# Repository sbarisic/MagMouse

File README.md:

# MagMouse

An open-source wired mouse exploring contactless Hall-sensed buttons with plastic
click mechanisms, and a motorized haptic scroll wheel.

**Active development: [four two-layer boards](hardware/two-layer/sandwich/README.md),
with two 70 Ã— 100 mm stacked Main boards and passive plastic button clicks.**
All four boards are routed, with independent schematics and clean native
ERC, DRC, connectivity and schematic-parity checks under the saved rules.
The [quote package](hardware/two-layer/sandwich/quote-package/README.md) contains
Gerbers, drills, BOMs and placement files; supplier and physical acceptance remain open.
The Main stack and Wheel harness each use 19 wires with three shared grounds.

Superseded boards, bench fixtures and quote packages are available in
[Git history](docs/history/README.md). The current checkout contains the active
designs, shared libraries, current manufacturing exports and retained evidence.

## V1 concept

- ESP32-S3 with native USB Full-Speed HID; target report interval: 1 ms.
- PMW3360DM-T2QU + LM19-LSI optical sensor for cursor movement; ICM-42688-P for supplementary motion.
- Three plastic click mechanisms provide tactile feedback and passive return.
  Each uses a TMAG5253 Hall sensor and a sensing magnet, read through ADS7038.
  Buttons have no coils or powered force feedback.
- MA735 angle sensing and a GB1806 motor driven by DRV8316R for scroll haptics.
- One USB-C cable for data and 5 V power, with force limits based on detected
  source capability. A powered Type-C hub/adapter is the intended full-power source.

## Repository map

| Directory | Contents |
| --- | --- |
| [hardware](hardware/README.md) | Electronics, preliminary BOM, schematic and PCB work |
| [mechanical](mechanical/README.md) | Housing, button mechanisms, scroll assembly |
| [firmware](firmware/README.md) | Embedded architecture and bring-up plan |
| [software](software/README.md) | Future PC configuration application |
| [docs](docs/README.md) | Requirements, interfaces, power and roadmap |

Start with the [architecture](docs/architecture.md), [interface plan](docs/interfaces.md),
and [button prototype plan](mechanical/button-mechanisms/README.md), then the
[roadmap](docs/roadmap.md). [ideas.md](ideas.md) preserves the original
brainstorming notes; the organized documents distinguish selected directions from
open engineering questions.

## Contributing and licensing

See [CONTRIBUTING.md](CONTRIBUTING.md). The next milestone is mechanical-interface
CAD, resulting PCB adjustments and whole-board review before manufacturing closure.

Hardware/mechanical: **CERN-OHL-S-2.0**. Firmware, PC software and supporting code:
**GPL-3.0-or-later**. General documentation: **CC-BY-SA-4.0**.
See [LICENSE.md](LICENSE.md) for scope and full texts.

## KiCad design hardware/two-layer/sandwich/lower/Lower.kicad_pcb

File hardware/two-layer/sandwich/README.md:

# MagMouse stacked two-layer boards

All four boards are routed and have independent schematics. Native KiCad 10.0.6
checks report zero ERC findings, DRC findings, unconnected items and schematic
parity findings under the saved rules. The [quote package](quote-package/README.md)
contains the files for supplier pricing; physical and supplier acceptance remain open.

The active boards use 1206 packages for all 193 resistors and ceramic capacitors
that previously used 0603 or 0805. Values and pin/net assignments are unchanged.
[1206-PARTS.md](1206-PARTS.md) lists the replacement manufacturer part numbers,
ratings and sourcing status. [1206-review.json](1206-review.json) records the
earlier package migration; [assembly-spacing-review.json](assembly-spacing-review.json)
records the subsequent 2 mm component spacing and outline changes.

The standard-via revision uses 0.30 mm via drills and at least 0.45 mm copper
lands. All four boards are checked for via-hole/SMD-land overlaps. The derived
[238 × 114 mm panel](panel/Panel.kicad_pcb) combines one of each board using
2 mm routed gaps and 5 mm mouse-bite tabs. Source copper is copied exactly,
with isolated net names for each board; individual outlines remain unchanged.

| Board/project | Dimensions | Copper layers | Original circuit footprints | Added interface/mount footprints |
| --- | --- | ---: | ---: | ---: |
| [Lower](lower/Lower.kicad_pro) | 70 × 100 mm, tapered | 2 | 122 | 6 |
| [Upper](upper/Upper.kicad_pro) | 70 × 100 mm, tapered | 2 | 86 | 6 |
| [Wheel](wheel/Wheel.kicad_pro) | 70 × 67 mm, clipped Main profile | 2 | 87 | 0 |
| [Encoder](../encoder/Encoder.kicad_pro) | 14 × 18 mm, two 4 mm upper chamfers | 2 | 3 | 0 |

[All-board overview](all-boards.png). Component footprints, pads and drills are
full size. Both Main outlines retain the approved taper and 38.5 mm front edge.
Wheel follows the Main sidewalls between y = 26 and 93 mm. Its 4,448 mm² outline adds 1,148 mm² to the previous rectangle. Wheel coordinates plus (7.5, 29) mm align it with Main in plan view. Stack height and Wheel mounting need mechanical fit confirmation.

[Wheel power and ground review](routing-review/POWER-GROUND.md) covers trace necks, via barrels, GND pours and the reordered brake feedback resistors.

[3D exports](3d/README.md) include STEP, GLB and angled previews for each board
and the panel, plus bare substrate STEP files. The populated exports include
available library models; the coverage report identifies 14 missing component
bodies. These are PCB models, not a mechanically positioned mouse assembly.

## Circuit and schematic split

Lower contains the ESP32, USB connector and data/CC circuitry, 3.3 V regulator,
optical sensor and local supplies, IMU, RGB, encoder interface and Wheel signal
connector J8. Upper contains the eFuses, power monitoring, three Hall sensors,
ADC1, hardware interlock and Wheel power connector J10.

The independent [Lower schematic](lower/Lower.kicad_sch) and
[Upper schematic](upper/Upper.kicad_sch) each include `20_Stack_Harness` with the
actual signal/power arrays and mounting holes. PCB symbol paths match these
projects. The combined [Main circuit](main-circuit/Main.kicad_sch) is retained as
the migration reference; edit the independent projects for subsequent work.
Every retained component value and pin/net connection was compared with that
reference. USB data/CC and analog Hall/current-sense/ADC connections stay local
to their respective boards.

Buttons use passive plastic click mechanisms and one sensing magnet per Hall
sensor. The active design removes 38 button-only parts, including U4/U5/U6,
J2/J3/J4 and U17. ADC1 channels 3–5 are grounded spares; GPIO4–9 are unused.
U18 retains the shared HALL_EN gate. Wheel drive, interlock, ACT_5V protection
and shared storage remain. [passive-buttons.json](passive-buttons.json) records
the exact removed parts and pin changes. The older routed checkpoints retain
the superseded button-coil circuitry.

## Wiring

The Main stack has **19 wires with three shared grounds**:

| Interface | Signals/supplies | Grounds | Total |
| --- | ---: | ---: | ---: |
| J101 ↔ J102 | 13 signals | 1 | 14 |
| J103 ↔ J104 | 3 supply rails | 2 | 5 |

Connect equal pad numbers using [WIRE_MAP.md](WIRE_MAP.md). Signal arrays are
2 × 7 at 2.54 mm pitch: x = 6/8.54 mm, y = 42–57.24 mm, 1.8 mm lands and
0.8 mm drills. Five power pads use 5.08 mm pitch at x = 25–45.32 mm,
2.4 mm lands and 1.2 mm drills. Both power arrays moved together to y = 12.25 mm
to provide assembly space below USB. Raw VBUS goes up, PWR_5V returns to Lower and
+3V3 goes back up. ACT_5V stays on Upper and feeds Wheel.

The Wheel harness also has **19 wires with three shared grounds**. Lower J8
and Wheel J9 each use 17 pads in a 2 × 9 grid with one hole omitted; their copper
envelope is 22.12 × 4.34 mm. Upper J10 and Wheel J11 carry ACT_5V and the third
ground. See [WHEEL_WIRE_MAP.md](WHEEL_WIRE_MAP.md). Wire gauges, cut lengths and
stack height still depend on the mechanical assembly.

## Placement and routing

Separate front components have at least 2 mm between their body-and-solder-land
envelopes. This does not change the pitch of pins within an IC or wire array;
copper-only test access is excluded from the component spacing measurement.
The circled Upper passive group has at least 3 mm clearance to the board edge.
The layouts retain the USB, optical, Hall, antenna and mounting datums. The two
stack power arrays move together by 1.25 mm; their pitch and pin map are unchanged.
Other parts and colliding front test pads move as recorded in the spacing review.
Fitted electronic parts remain on the front; several diagnostic test pads are
on the back. Encoder retains its sensor and wire-array positions; its two
4 × 4 mm chamfers remove 16 mm², reducing outline area from 252 to 236 mm².

The long USB pair was placed before routing, around the right side of the
optical reserve, using the inherited 1.10 mm trunk width and 0.15 mm nominal
gap with narrow land escapes. The 1206 revision retains that corridor and adapts
the resistor-end escape. Freerouting 2.5.0 and local geometric routing helpers
rebuilt connections affected by the larger packages. KiCad then checked minimum
track/via sizes, filled and stitched ground copper,
removed unused fanout vias, and checked actual connectivity and clearances.
Power escapes were widened where geometry permits. The fabricator's stack and
physical USB, power, thermal and analog performance still need verification.

Aligned M2 mounting candidates remain at (18,6), (52,6), (7,76), (63,76) mm:
2.2 mm holes and 5 mm support envelopes. Lower now has a real 17.26 × 8.60 mm
optical opening on Edge.Cuts, following PixArt PMW3360 datasheet R1.50 Figure 3.
In board coordinates it spans x = 31.20–39.80 and y = 43.68–60.94 mm; U35's
optical center remains (35.5,52.5) mm. Internal corners use R1 mm for the panel's
nominal 2 mm router; this corner geometry requires lens-fit confirmation.
The lens faces downward through Lower,
so this does not add a duplicate opening to Upper. Lens retention and stack
height still need mechanical fit confirmation. U3 stays at (35,89.25) mm,
with its antenna approximately 0.43 mm from
the curved board edge at the corners. The requested 5 mm reserve is
x = 22.3–47.7, y = 94.5–104 mm on both boards, extending beyond the rear edge.
Upper retains substrate over that region; assembled radio performance is untested.

## Validation and quote files

[routing-review/summary.json](routing-review/summary.json) records current board
hashes, sizes, layer counts, ERC/DRC/parity results and fabrication dimensions.
The native reports, exported netlists, front/back copper SVGs and track-width
measurements are alongside it. Inherited ignored categories remain explicit in
the reports; no new DRC or ERC exclusions were added for routing.

[MagMouse-quote-package.zip](MagMouse-quote-package.zip) includes four separate
Gerber/drill ZIPs, per-board BOM/CPL CSVs, combined purchasing inventory, manual
items and via-in-pad intersection lists. Read its [quotation notes](quote-package/README.md)
for stack, assembly, stock, shipping/tax and mechanical assumptions. This is a
pricing package. The [first live quote](quotes/2026-11-04-jlcpcb/QUOTE.md) records
the superseded 0.20 mm, separate-board version. The [standard-via panel quote](quotes/2026-11-04-panel-standard-vias/QUOTE.md)
was EUR 42.83 for five complete sets, or USD 99.25 delivered by EuroPacket DDP
to Croatia (4 November 2026). That quote predates the 1206 migration and has not
been refreshed for these files. No fabrication order is placed.

`partition.json` preserves ownership and the checked 19-wire contract.
`placement-positions.json`, `spacing-review.json`, `spacing-baseline.json`,
`placement.svg/png` and `passive-validation.json` are historical pre-routing
evidence; their old board hashes and airwire counts are not current route results.

## Reproduction

Use KiCad 10 Python. Edit the independent KiCad projects for future circuit or
layout changes. The one-time split and obsolete placement generators are now
in [Git history](../../../docs/history/README.md). Shared libraries and helper
functions live in [hardware/common](../../common/README.md).

`route_main.py` exports/imports Specctra sessions, `route_usb.py` defines the
initial USB corridor, `finish_main.py` fills and stitches ground, and
`widen_power.py` widens power where clearance and keepouts allow. Freerouting
2.5.0 used neck retry at 150 µm with the optimizer disabled for Lower. Lower's
DSN clearance was increased to 165 µm to leave margin for native minimum-width
restoration; saved KiCad clearances remain unchanged. Temporary sessions, router
binaries and logs stay in ignored `build/sandwich/main-routing`.

`export_quote.py` rechecks all four boards before exporting the package and
compares Main pins against the retained migration reference. `overview.py`
renders placement views; add `--main-only --copper` for the routed Main image.
The netlist and schematic-parity checks cover the current Wheel harness.
The obsolete harness conversion script is retained in Git history.

`standard_vias.py` records the one-time drill migration and assists local via
relocation; `repair_wheel.py` and `continuous_routes.py` provide local path repairs.
`standard-via-review.json` is historical evidence for the pre-1206 revision. It records unchanged component placement and pad/net identity,
unchanged motor-phase/brake copper, and the final drill and via-in-pad counts. The finished
KiCad boards are the editable source. `panelize.py` derives and verifies the
combined manufacturing panel and exports its Gerbers/drills. Its verification
compares every source pad, track, via drill and filled-zone vertex after translation,
checks connected substrate and router access, and runs native panel DRC.

`large_passives.py` performs the guarded one-time 1206 migration and verifies it
against the saved pre-migration snapshots in ignored `build/sandwich/1206`.
`1206-migration.json` records the per-reference purchasing substitutions;
`1206-review.json` records the final checks and source hashes. Do not rerun
the migration on an already converted project. `region_routes.py` supports
local two-layer repairs; every saved result still requires native KiCad DRC.

The fabrication rules explicitly use JLCPCB's 0.075 mm via annular ring and
0.20 mm via-hole-to-copper clearance, replacing 0.125/0.25 mm in the earlier
revision. Via hole-to-hole clearance stays 0.25 mm, copper clearance stays
0.15 mm by net class (0.127 mm board minimum), and minimum track width stays
0.127 mm. No additional DRC categories are ignored. These limits are based on
[JLCPCB's published capabilities](https://jlcpcb.com/capabilities/pcb-capabilities/).

Hardware: CERN-OHL-S-2.0. Scripts: GPL-3.0-or-later. Documentation: CC-BY-SA-4.0.

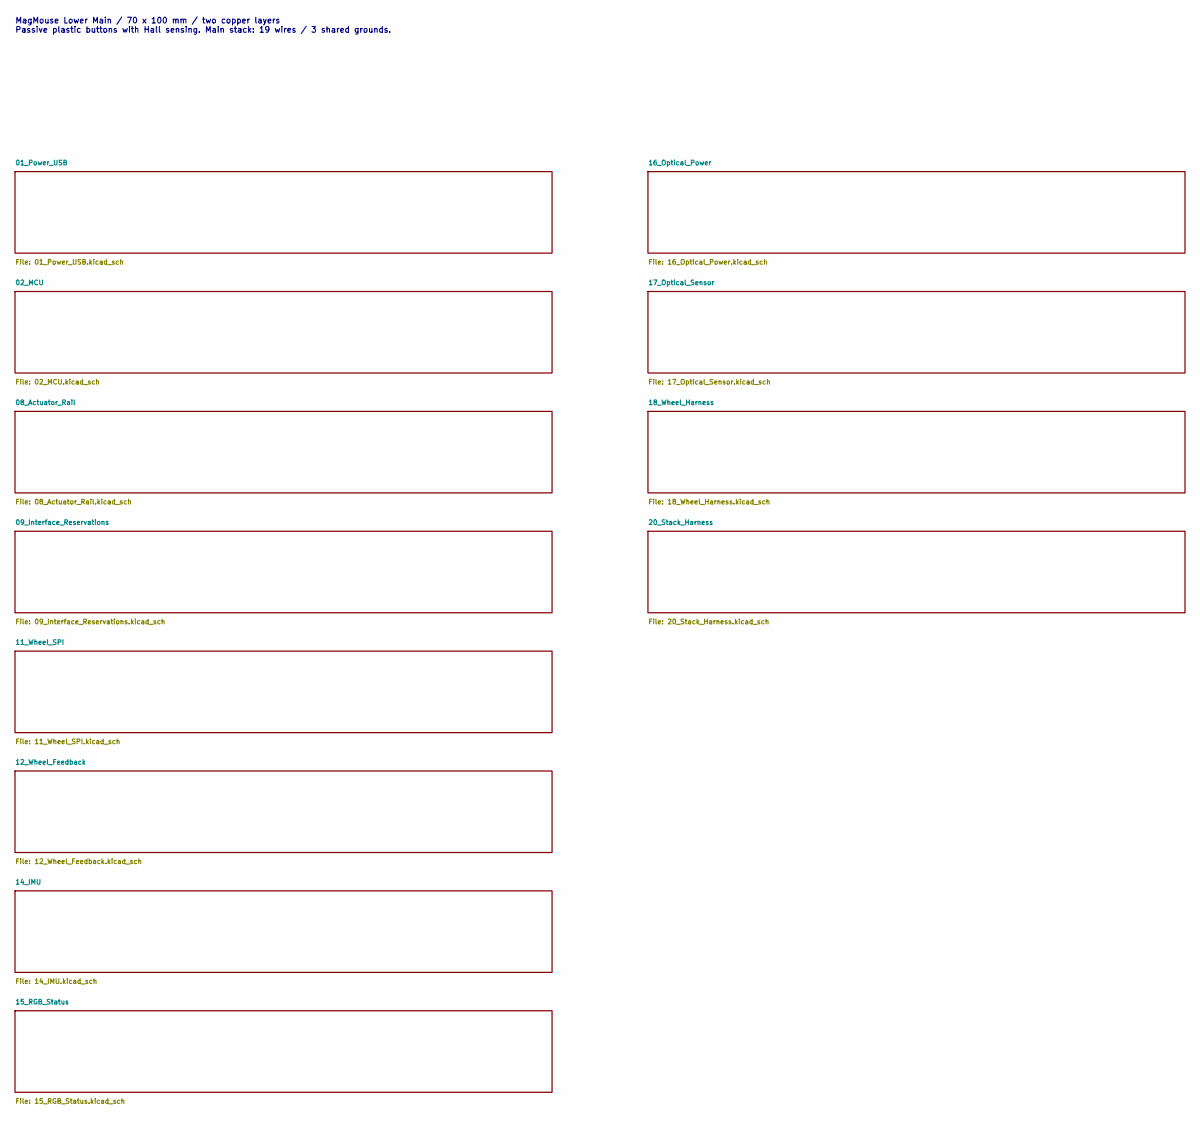
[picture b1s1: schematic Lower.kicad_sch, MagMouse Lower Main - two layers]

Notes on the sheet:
MagMouse Lower Main / 70 x 100 mm / two copper layers Passive plastic buttons with Hall sensing. Main stack: 19 wires / 3 shared grounds.

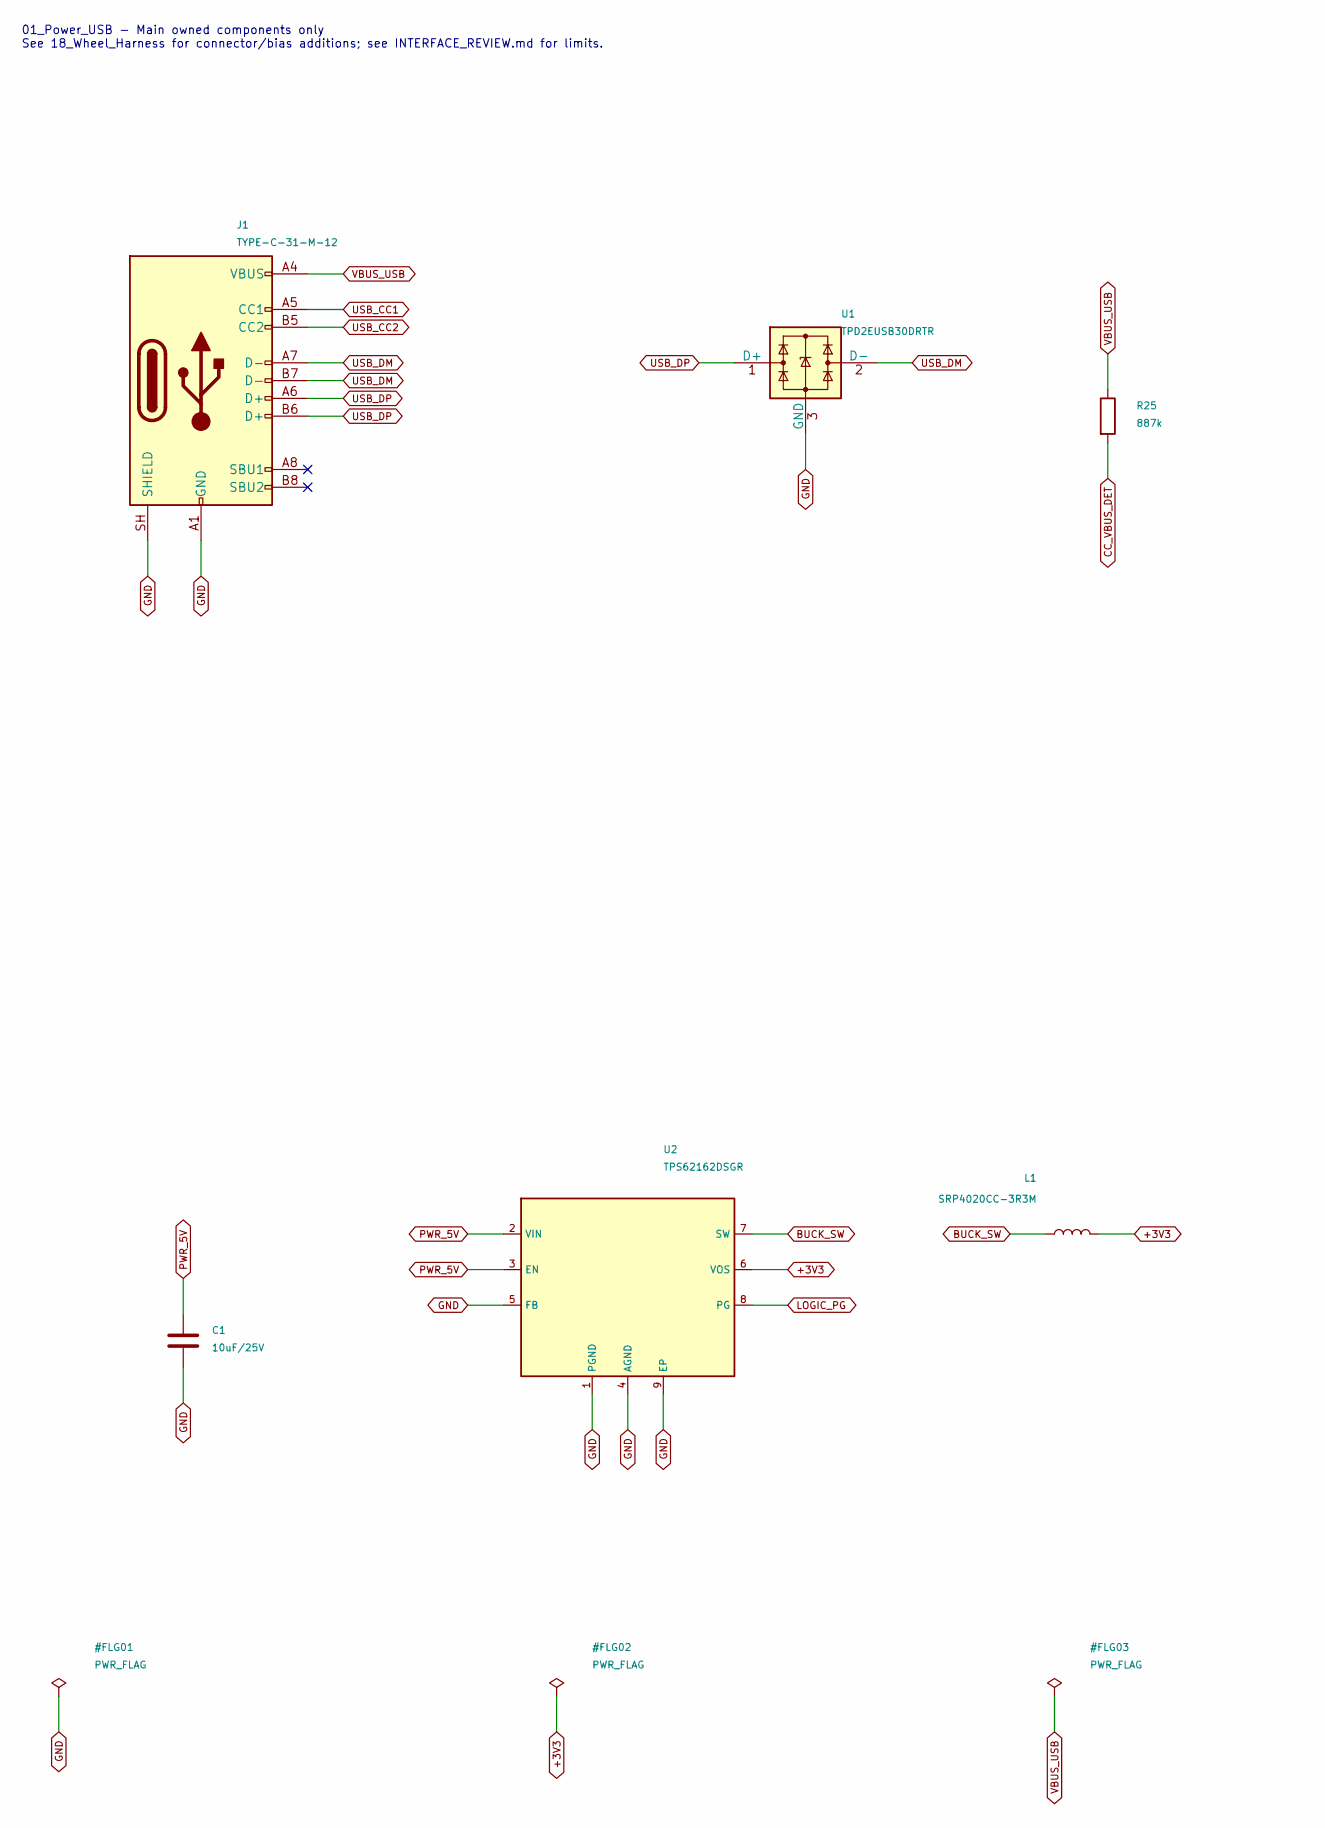
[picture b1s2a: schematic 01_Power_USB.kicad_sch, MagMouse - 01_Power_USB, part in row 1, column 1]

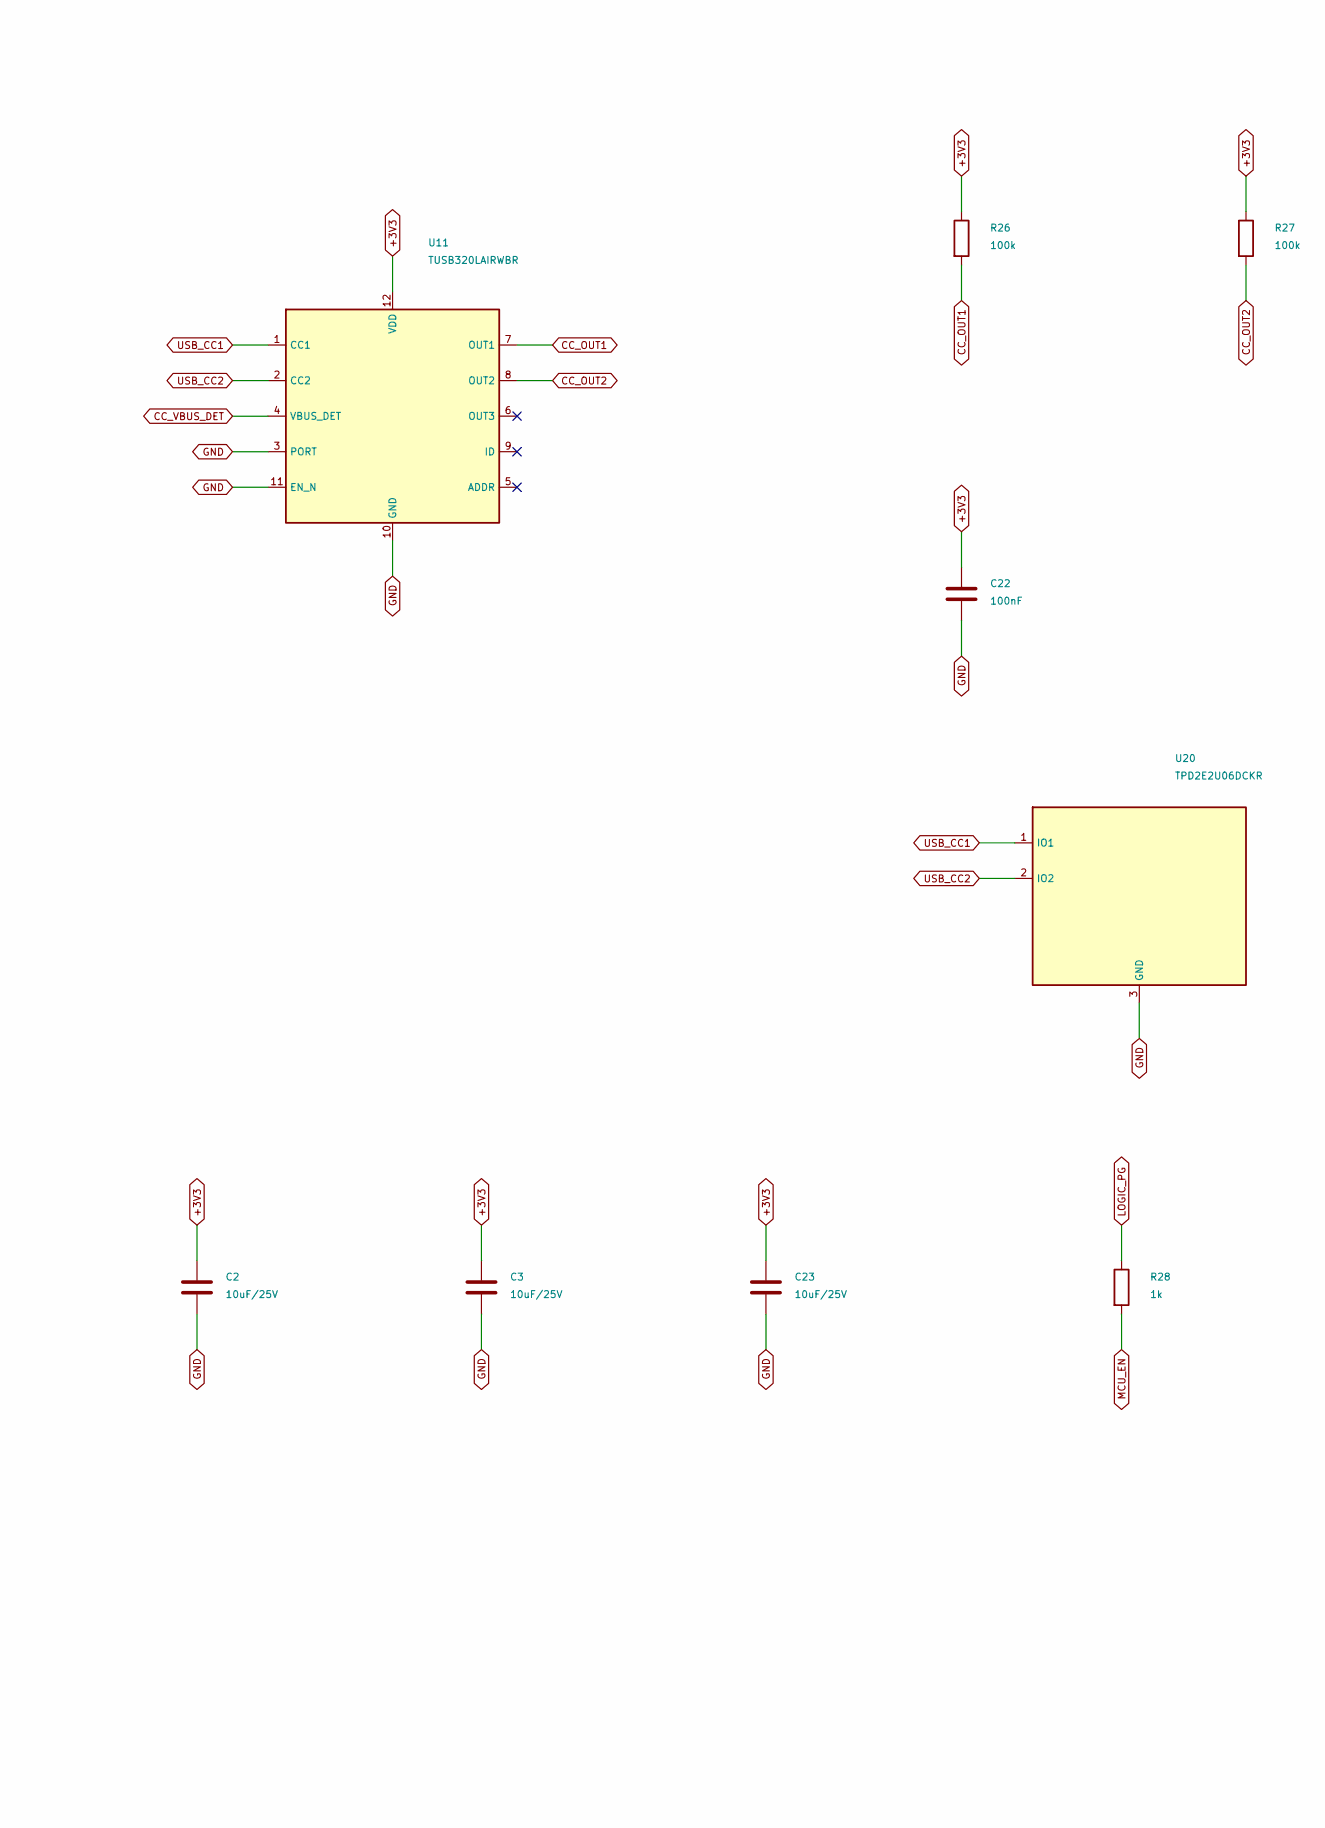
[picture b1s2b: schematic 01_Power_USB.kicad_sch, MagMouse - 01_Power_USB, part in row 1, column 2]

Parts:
C1, C2, C3, C23: 10uF/25V; C_1206_3216Metric; Rating 25 V, X5R, 10%; MPN CL31A106KAHNNNE
C22: 100nF; C_1206_3216Metric; Rating 50 V, X7R, 10%; MPN CC1206KRX7R9BB104
J1: TYPE-C-31-M-12; USB_C_Receptacle_HRO_TYPE-C-31-M-12; MPN TYPE-C-31-M-12; LCSC C165948
L1: SRP4020CC-3R3M; L_Bourns_SRP4020CC; MPN SRP4020CC-3R3M
R25: 887k; R_1206_3216Metric; Rating 0.25 W, 1%; MPN RC1206FR-07887KL
R26, R27: 100k; R_1206_3216Metric; Rating 0.25 W, 1%; MPN RC1206FR-07100KL
R28: 1k; R_1206_3216Metric; Rating 0.25 W, 1%; MPN RC1206FR-071KL
U1: TPD2EUSB30DRTR; Texas_DRT-3; MPN TPD2EUSB30DRTR; LCSC C97502
U2: TPS62162DSGR; Texas_DSG0008A_WSON-8-1EP_2x2mm_P0.5mm_EP0.9x1.6mm; MPN TPS62162DSGR; LCSC C40256
U11: TUSB320LAIRWBR; Texas_X2QFN-12_1.6x1.6mm_P0.4mm; MPN TUSB320LAIRWBR; LCSC C132554
U20: TPD2E2U06DCKR; SOT-323_SC-70; MPN TPD2E2U06DCKR; LCSC C1855726

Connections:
+3V3: C2.1, C3.1, C22.1, C23.1, L1.2, R26.1, R27.1, U2.6 (VOS), U11.12 (VDD); also elsewhere on the board
BUCK_SW: L1.1, U2.7 (SW)
CC_OUT1: R26.2, U11.7 (OUT1); also elsewhere on the board
CC_OUT2: R27.2, U11.8 (OUT2); also elsewhere on the board
CC_VBUS_DET: R25.2, U11.4 (VBUS_DET)
GND: C1.2, C2.2, C3.2, C22.2, C23.2, J1.A1 (GND), J1.A12 (GND), J1.B1 (GND), J1.B12 (GND), J1.SH (SHIELD), U1.3 (GND), U2.1 (PGND), U2.4 (AGND), U2.5 (FB), U2.9 (EP), U11.3 (PORT), U11.10 (GND), U11.11 (EN_N), U20.3 (GND); also elsewhere on the board
LOGIC_PG: R28.1, U2.8 (PG)
MCU_EN: R28.2; also elsewhere on the board
PWR_5V: C1.1, U2.2 (VIN), U2.3 (EN); also elsewhere on the board
USB_CC1: J1.A5 (CC1), U11.1 (CC1), U20.1 (IO1)
USB_CC2: J1.B5 (CC2), U11.2 (CC2), U20.2 (IO2)
USB_DM: J1.A7 (D-), J1.B7 (D-), U1.2 (D-); also elsewhere on the board
USB_DP: J1.A6 (D+), J1.B6 (D+), U1.1 (D+); also elsewhere on the board
VBUS_USB: J1.A4 (VBUS), J1.A9 (VBUS), J1.B4 (VBUS), J1.B9 (VBUS), R25.1; also elsewhere on the board

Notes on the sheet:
01_Power_USB - Main owned components only See 18_Wheel_Harness for connector/bias additions; see INTERFACE_REVIEW.md for limits.

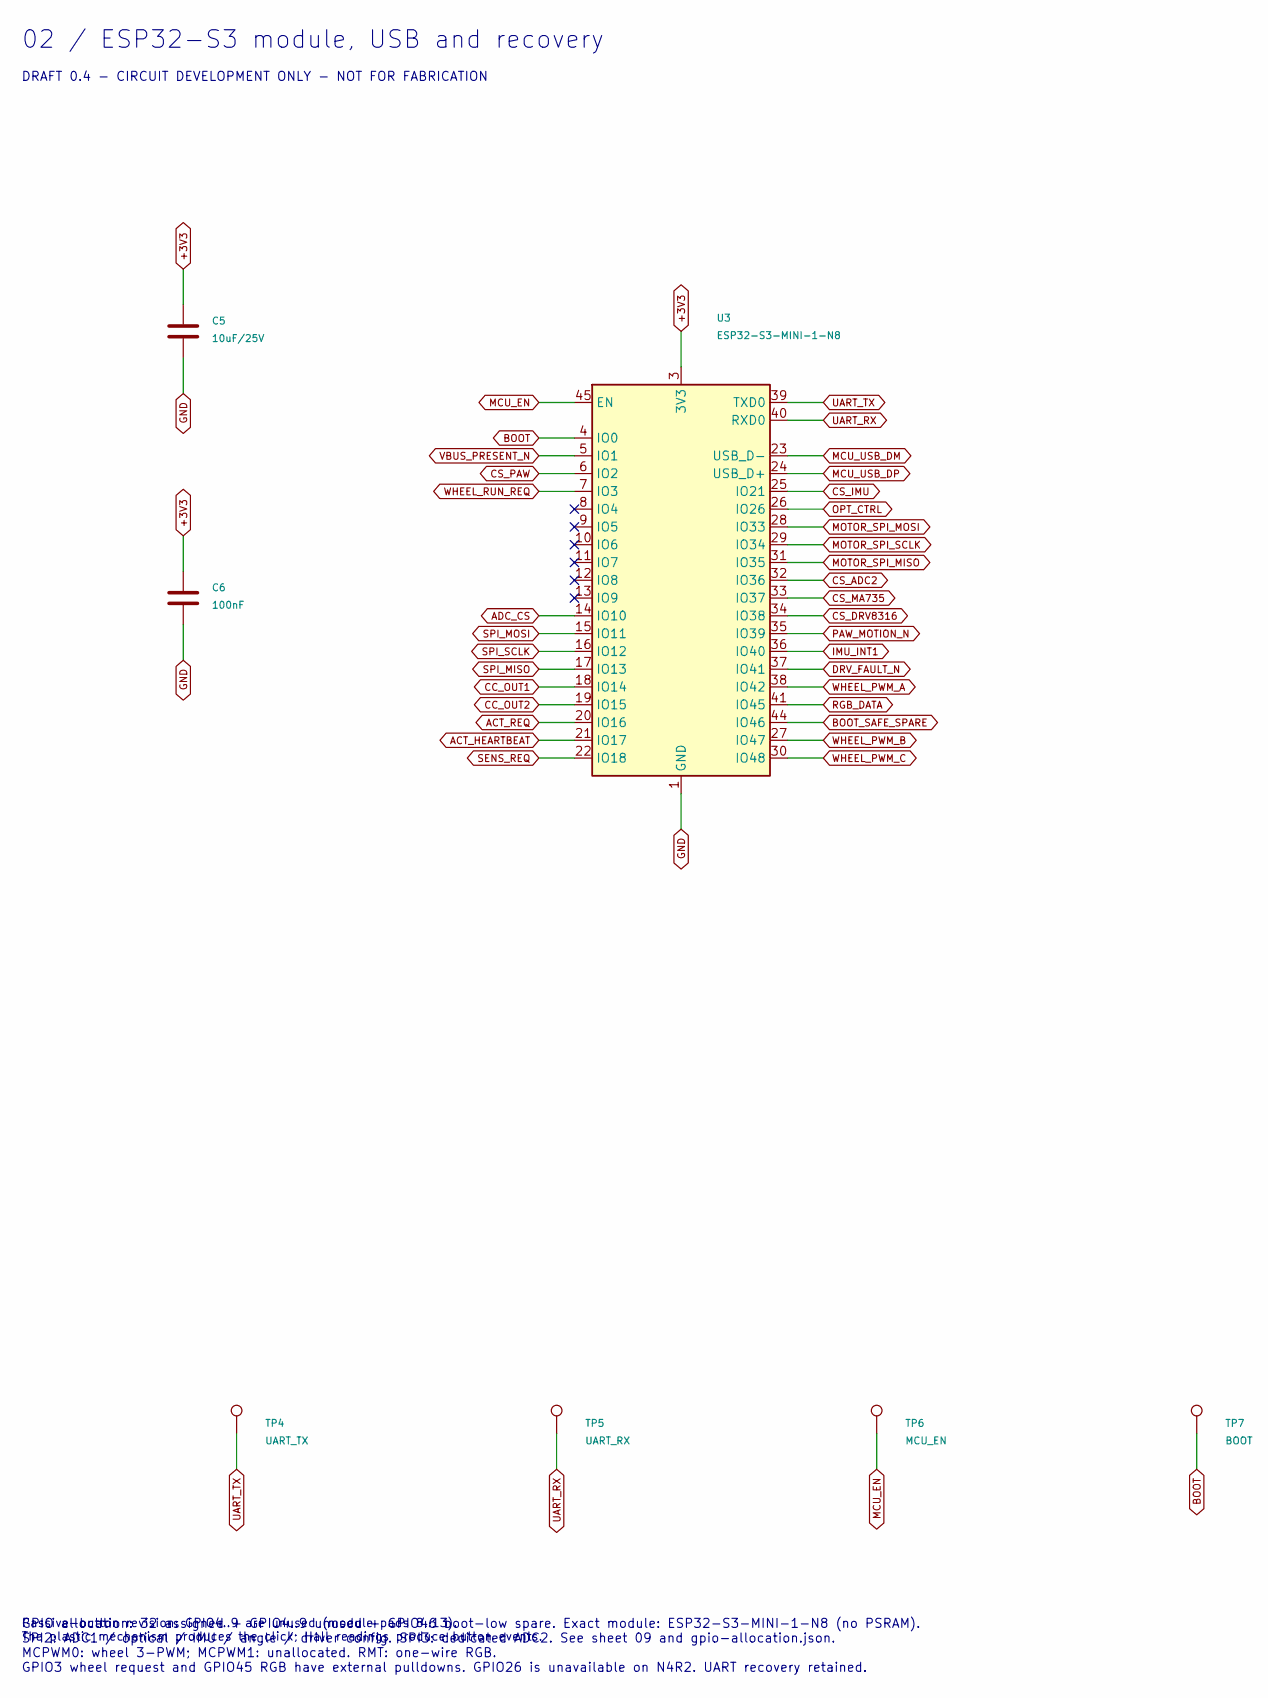
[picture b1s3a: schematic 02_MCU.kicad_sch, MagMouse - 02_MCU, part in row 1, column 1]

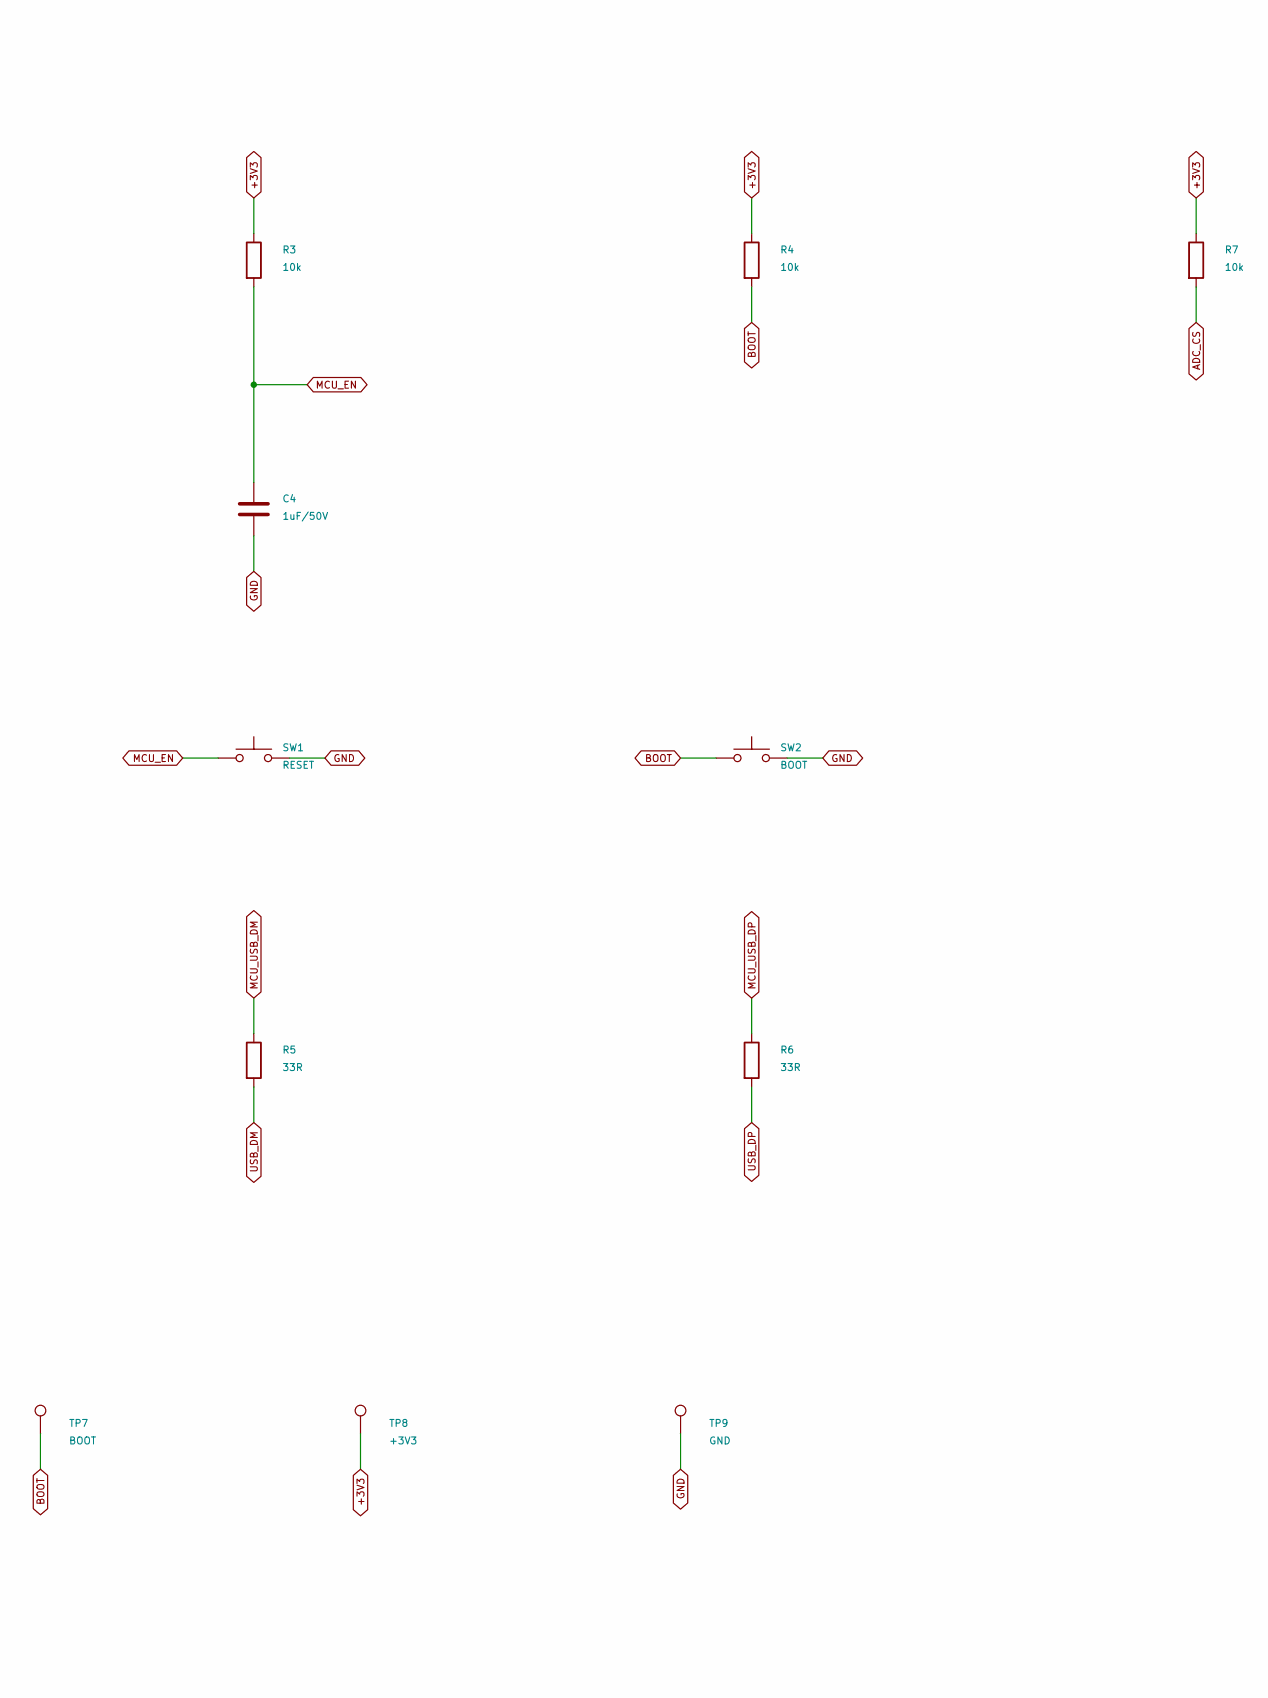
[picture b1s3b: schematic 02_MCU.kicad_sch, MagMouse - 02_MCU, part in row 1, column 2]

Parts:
C4: 1uF/50V; C_1206_3216Metric; Rating 50 V, X7R, 10%; MPN CL31B105KBHNNNE; JLCPCB Library Type Basic
C5: 10uF/25V; C_1206_3216Metric; Rating 25 V, X5R, 10%; MPN CL31A106KAHNNNE
C6: 100nF; C_1206_3216Metric; Rating 50 V, X7R, 10%; MPN CC1206KRX7R9BB104
R3, R4, R7: 10k; R_1206_3216Metric; Rating 0.25 W, 1%; MPN RC1206FR-0710KL
R5, R6: 33R; R_1206_3216Metric; Rating 0.25 W, 1%; MPN RC1206FR-0733RL
SW1: RESET; SW_SPST_TS-1088-xR020; MPN TS-1088-AR02016; LCSC C720477
SW2: BOOT; SW_SPST_TS-1088-xR020; MPN TS-1088-AR02016; LCSC C720477
TP4: UART_TX; TestPoint_Pad_D1.0mm
TP5: UART_RX; TestPoint_Pad_D1.0mm
TP6: MCU_EN; TestPoint_Pad_D1.0mm
TP7: BOOT; TestPoint_Pad_D1.0mm
TP8: +3V3; TestPoint_Pad_D1.0mm
TP9: GND; TestPoint_Pad_D1.0mm
U3: ESP32-S3-MINI-1-N8; ESP32-S2-MINI-1; MPN ESP32-S3-MINI-1-N8; LCSC C2913206

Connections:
+3V3: C5.1, C6.1, R3.1, R4.1, R7.1, TP8.1, U3.3 (3V3); also elsewhere on the board
ACT_HEARTBEAT: U3.21 (IO17); also elsewhere on the board
ACT_REQ: U3.20 (IO16); also elsewhere on the board
ADC_CS: R7.2, U3.14 (IO10); also elsewhere on the board
BOOT: R4.2, SW2.1, TP7.1, U3.4 (IO0)
BOOT_SAFE_SPARE: U3.44 (IO46); also elsewhere on the board
CC_OUT1: U3.18 (IO14); also elsewhere on the board
CC_OUT2: U3.19 (IO15); also elsewhere on the board
CS_ADC2: U3.32 (IO36); also elsewhere on the board
CS_DRV8316: U3.34 (IO38); also elsewhere on the board
CS_IMU: U3.25 (IO21); also elsewhere on the board
CS_MA735: U3.33 (IO37); also elsewhere on the board
CS_PAW: U3.6 (IO2); also elsewhere on the board
DRV_FAULT_N: U3.37 (IO41); also elsewhere on the board
GND: C4.2, C5.2, C6.2, SW1.2, SW2.2, TP9.1, U3.1 (GND), U3.2 (GND), U3.42 (GND), U3.43 (GND), U3.46 (GND), U3.47 (GND), U3.48 (GND), U3.49 (GND), U3.50 (GND), U3.51 (GND), U3.52 (GND), U3.53 (GND), U3.54 (GND), U3.55 (GND), U3.56 (GND), U3.57 (GND), U3.58 (GND), U3.59 (GND), U3.60 (GND), U3.61 (GND), U3.62 (GND), U3.63 (GND), U3.64 (GND), U3.65 (GND); also elsewhere on the board
IMU_INT1: U3.36 (IO40); also elsewhere on the board
MCU_EN: C4.1, R3.2, SW1.1, TP6.1, U3.45 (EN); also elsewhere on the board
MCU_USB_DM: R5.1, U3.23 (USB_D-)
MCU_USB_DP: R6.1, U3.24 (USB_D+)
MOTOR_SPI_MISO: U3.31 (IO35); also elsewhere on the board
MOTOR_SPI_MOSI: U3.28 (IO33); also elsewhere on the board
MOTOR_SPI_SCLK: U3.29 (IO34); also elsewhere on the board
OPT_CTRL: U3.26 (IO26); also elsewhere on the board
PAW_MOTION_N: U3.35 (IO39); also elsewhere on the board
RGB_DATA: U3.41 (IO45); also elsewhere on the board
SENS_REQ: U3.22 (IO18); also elsewhere on the board
SPI_MISO: U3.17 (IO13); also elsewhere on the board
SPI_MOSI: U3.15 (IO11); also elsewhere on the board
SPI_SCLK: U3.16 (IO12); also elsewhere on the board
UART_RX: TP5.1, U3.40 (RXD0)
UART_TX: TP4.1, U3.39 (TXD0)
USB_DM: R5.2; also elsewhere on the board
USB_DP: R6.2; also elsewhere on the board
VBUS_PRESENT_N: U3.5 (IO1); also elsewhere on the board
WHEEL_PWM_A: U3.38 (IO42); also elsewhere on the board
WHEEL_PWM_B: U3.27 (IO47); also elsewhere on the board
WHEEL_PWM_C: U3.30 (IO48); also elsewhere on the board
WHEEL_RUN_REQ: U3.7 (IO3); also elsewhere on the board

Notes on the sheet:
02 / ESP32-S3 module, USB and recovery
DRAFT 0.4 - CIRCUIT DEVELOPMENT ONLY - NOT FOR FABRICATION
GPIO allocation: 32 assigned + GPIO4..9 unused + GPIO46 boot-low spare. Exact module: ESP32-S3-MINI-1-N8 (no PSRAM). SPI2: ADC1 / optical / IMU / angle / driver config. SPI3: dedicated ADC2. See sheet 09 and gpio-allocation.json. MCPWM0: wheel 3-PWM; MCPWM1: unallocated. RMT: one-wire RGB. GPIO3 wh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
Passive-button revision: GPIO4..9 are unused (module pads 8..13). The plastic mechanism produces the click; Hall readings produce button events.

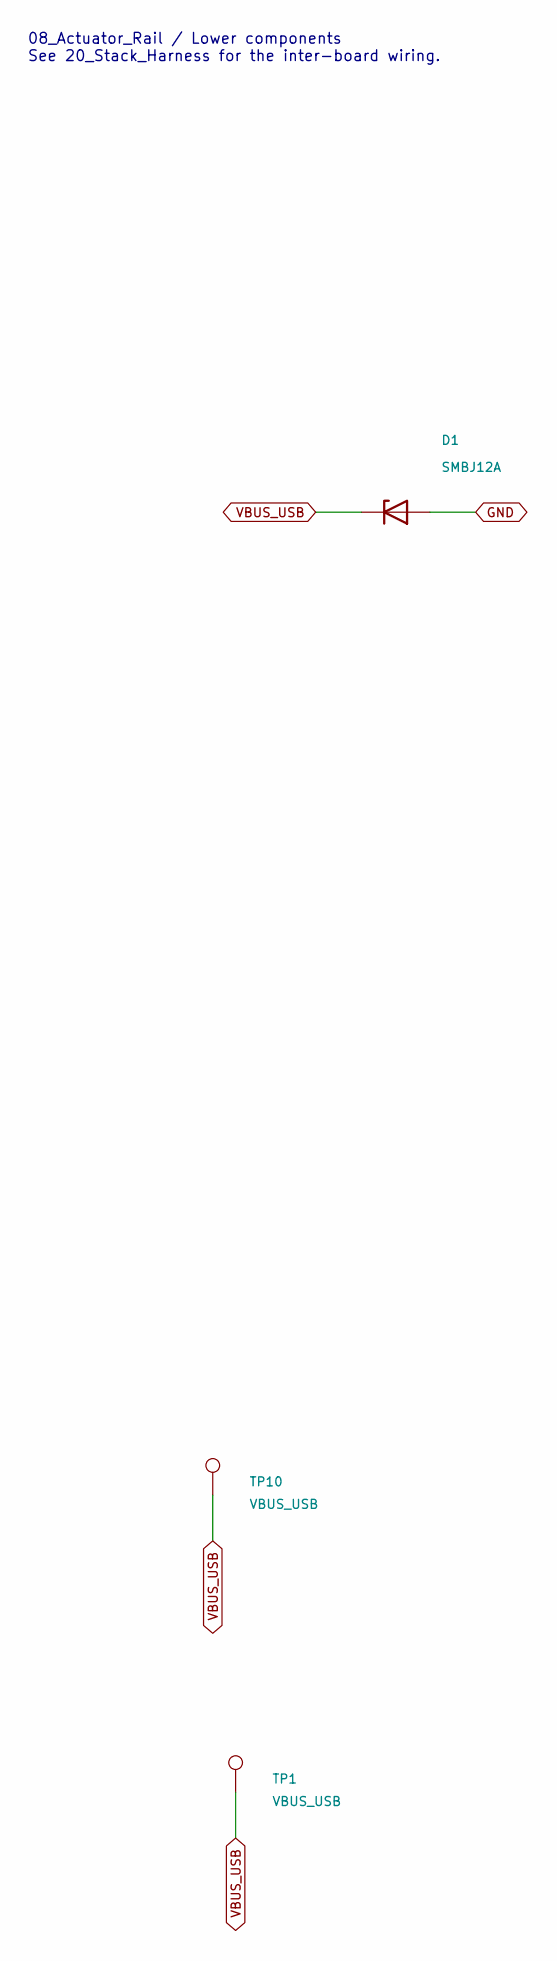
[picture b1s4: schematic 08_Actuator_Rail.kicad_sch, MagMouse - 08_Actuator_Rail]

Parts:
D1: SMBJ12A; D_SMB; MPN SMBJ12A; LCSC C151251
TP1, TP10: VBUS_USB; TestPoint_Pad_D1.0mm

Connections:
GND: D1.2 (A); also elsewhere on the board
VBUS_USB: D1.1 (K), TP1.1, TP10.1; also elsewhere on the board

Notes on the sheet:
08_Actuator_Rail / Lower components See 20_Stack_Harness for the inter-board wiring.
